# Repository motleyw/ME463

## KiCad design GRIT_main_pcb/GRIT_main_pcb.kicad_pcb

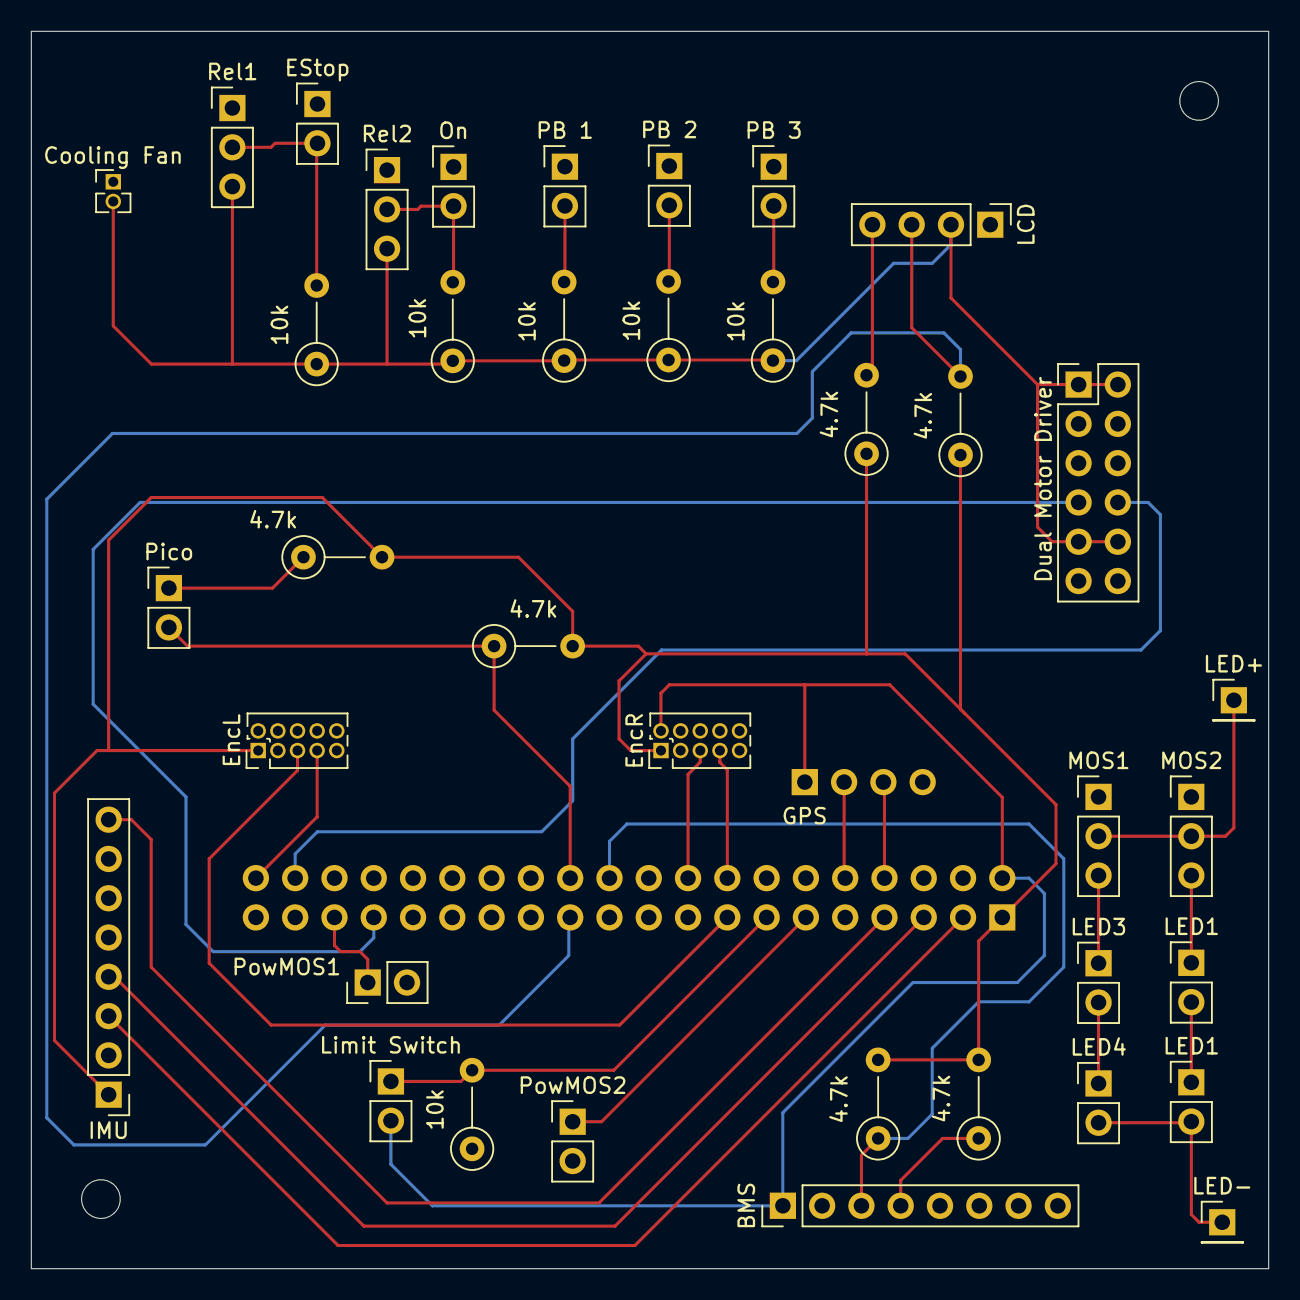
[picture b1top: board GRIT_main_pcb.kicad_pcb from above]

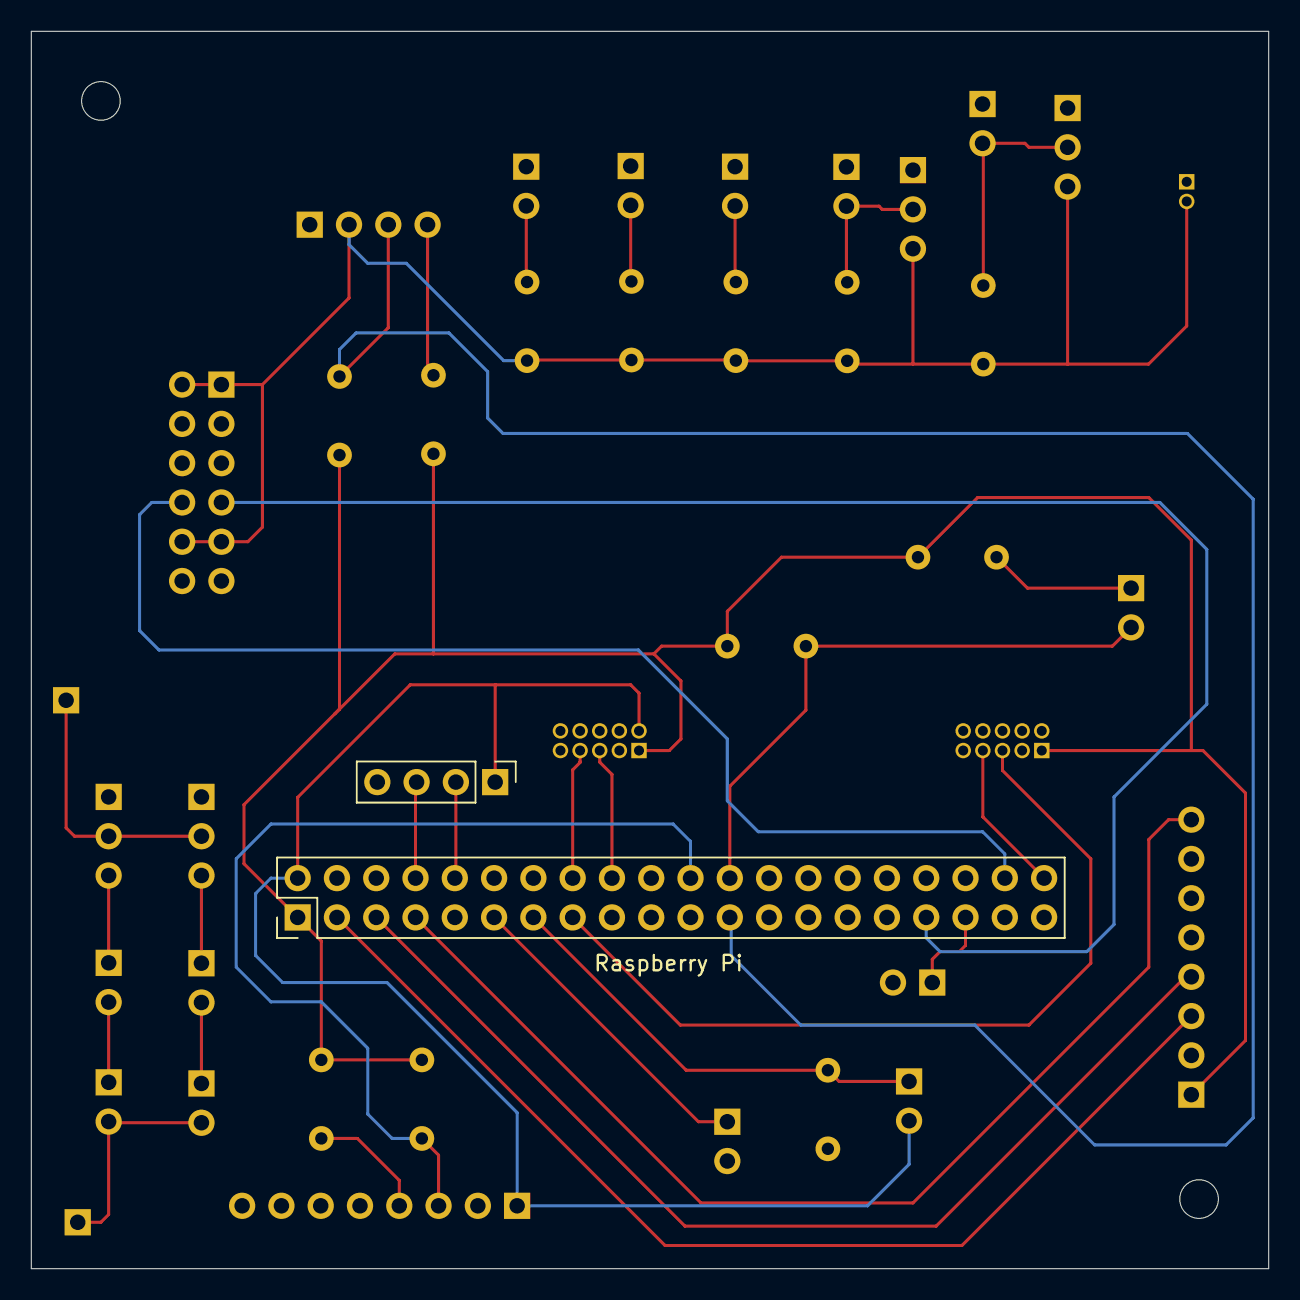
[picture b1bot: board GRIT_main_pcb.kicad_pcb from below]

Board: 4 copper layers, 80.0 x 80.0 mm, 40 parts (2 on the bottom side), 38 nets.

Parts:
4.7k: BMS SCL; R_Axial_DIN0207_L6.3mm_D2.5mm_P5.08mm_Vertical
4.7k#2: Pico SDA; R_Axial_DIN0207_L6.3mm_D2.5mm_P5.08mm_Vertical
4.7k#3: BMS SDA; R_Axial_DIN0207_L6.3mm_D2.5mm_P5.08mm_Vertical
4.7k#4: HMI SDA; R_Axial_DIN0207_L6.3mm_D2.5mm_P5.08mm_Vertical
4.7k#5: Pico SCL; R_Axial_DIN0207_L6.3mm_D2.5mm_P5.08mm_Vertical
4.7k#6: HMI SCL; R_Axial_DIN0207_L6.3mm_D2.5mm_P5.08mm_Vertical
10k: PB 2 Pull Down; R_Axial_DIN0207_L6.3mm_D2.5mm_P5.08mm_Vertical
10k#2, 10k#5: PB 1 Pull Down; R_Axial_DIN0207_L6.3mm_D2.5mm_P5.08mm_Vertical
10k#3, 10k#6: On/Off Pull Down; R_Axial_DIN0207_L6.3mm_D2.5mm_P5.08mm_Vertical
10k#4: PB 3 Pull Down; R_Axial_DIN0207_L6.3mm_D2.5mm_P5.08mm_Vertical
BMS: BMS Connector; PinHeader_1x08_P2.54mm_Vertical
Cooling Fan: Cooling Fan Connection; PinHeader_1x02_P1.27mm_Vertical
Dual Motor Driver: Motor Driver Connection; PinHeader_2x06_P2.54mm_Vertical
EStop: E-Stop; PinHeader_1x02_P2.54mm_Vertical
EncL: Motor Encoder; PinHeader_2x05_P1.27mm_Vertical
EncR: Motor Encoder; PinHeader_2x05_P1.27mm_Vertical
GPS: GPS Connector; PinHeader_1x04_P2.54mm_Vertical
IMU: IMU Connector; PinHeader_1x08_P2.54mm_Vertical
LCD: LCD Screen; PinHeader_1x04_P2.54mm_Vertical
LED1: LED 2; PinHeader_1x02_P2.54mm_Vertical
LED1#2, LED3, LED4: LED 1; PinHeader_1x02_P2.54mm_Vertical
LED+: LED+; PinHeader_1x01_P2.54mm_Vertical
LED-: LED-; PinHeader_1x01_P2.54mm_Vertical
Limit Switch: Limit Switch; PinHeader_1x02_P2.54mm_Vertical
MOS1, MOS2: LED Transistor; PinHeader_1x03_P2.54mm_Vertical
On: On/Off; PinHeader_1x02_P2.54mm_Vertical
PB 1, PB 2, PB 3: PB 1; PinHeader_1x02_P2.54mm_Vertical
Pico: Pico Connection; PinHeader_1x02_P2.54mm_Vertical
PowMOS1: Power Mosfet 1; PinHeader_1x02_P2.54mm_Vertical
PowMOS2: Power Mosfet 2; PinHeader_1x02_P2.54mm_Vertical
Raspberry Pi: PinHeader_2x20_P2.54mm_Vertical
Rel1, Rel2: PinHeader_1x03_P2.54mm_Vertical

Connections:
3V3: 4.7k.2, 4.7k#2.2, 4.7k#3.2, 4.7k#4.1, 4.7k#5.2, 4.7k#6.1, EncL.1, EncR.1, IMU.1, Raspberry Pi.1
5V: 10k.1, 10k#3.1, 10k#4.1, 10k#5.1, 10k#6.1, BMS.1, Cooling Fan.2, Dual Motor Driver.1, Dual Motor Driver.2, Dual Motor Driver.9, Dual Motor Driver.10, EncL.2, EncR.2, GPS.1, LCD.2, Limit Switch.2, Raspberry Pi.2, Rel1.3, Rel2.3
EStop: 10k#6.2, EStop.2, Rel1.2
GND: 10k#2.1, BMS.2, Cooling Fan.1, Dual Motor Driver.3, Dual Motor Driver.4, EStop.1, EncL.10, EncR.10, GPS.4, IMU.2, LCD.1, On.1, PB 1.1, PB 2.1, PB 3.1, PowMOS1.2, PowMOS2.2, Raspberry Pi.39, Rel1.1, Rel2.1
LED1: LED1.1, MOS2.3
LED2: LED1.2, LED1#2.1
LED3: LED3.1, MOS1.3
LED4: LED3.2, LED4.1
LED+: LED+.1, MOS1.2, MOS2.2
LED-: LED1#2.2, LED4.2, LED-.1
On: 10k#3.2, On.2, Rel2.2
PI3: IMU.3, Raspberry Pi.3
PI5: IMU.4, Raspberry Pi.5
PI7: IMU.8, Raspberry Pi.7
PI8: GPS.3, Raspberry Pi.8
PI10: GPS.2, Raspberry Pi.10
PI11: PowMOS2.1, Raspberry Pi.11
PI12: Dual Motor Driver.6, Raspberry Pi.12
PI13: 10k#2.2, Limit Switch.1, Raspberry Pi.13
PI15: EncL.5, Raspberry Pi.15
PI16: EncR.7, Raspberry Pi.16
PI18: EncR.5, Raspberry Pi.18
PI19: 4.7k#6.2, LCD.4, Raspberry Pi.19
PI21: 4.7k#5.1, Pico.1, Raspberry Pi.21
PI22: 4.7k.1, BMS.3, Raspberry Pi.22
PI23: 4.7k#4.2, LCD.3, Raspberry Pi.23
PI24: 4.7k#2.1, Pico.2, Raspberry Pi.24
PI26: 10k.2, PB 2.2, Raspberry Pi.26
PI28: 10k#5.2, PB 1.2, Raspberry Pi.28
PI29: 10k#4.2, PB 3.2, Raspberry Pi.29
PI31: MOS2.1, Raspberry Pi.31
PI32: Dual Motor Driver.5, Raspberry Pi.32
PI33: Dual Motor Driver.7, Raspberry Pi.33
PI35: PowMOS1.1, Raspberry Pi.35
PI36: MOS1.1, Raspberry Pi.36
PI37: 4.7k#3.1, BMS.4, Raspberry Pi.37
PI38: Dual Motor Driver.8, Raspberry Pi.38
PI40: EncL.7, Raspberry Pi.40

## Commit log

2025-02-27 Updated Schematic
2025-02-27 Autosave
2025-02-28 Updated Schematic
    Added GPS, IMU, and Ultrasonic sensors to schematic. Also wired the other two motor drivers to the motors.
2025-03-02 Updated Design
2025-03-04 Updated and Added PDF
2025-03-09 Final Schematic
2025-03-09 Minor Fix
2025-03-26 Main PCB Commit
2025-03-27 1st layer done
2025-03-27 Final Main PCB
2025-03-28 Sub PCB Updated
